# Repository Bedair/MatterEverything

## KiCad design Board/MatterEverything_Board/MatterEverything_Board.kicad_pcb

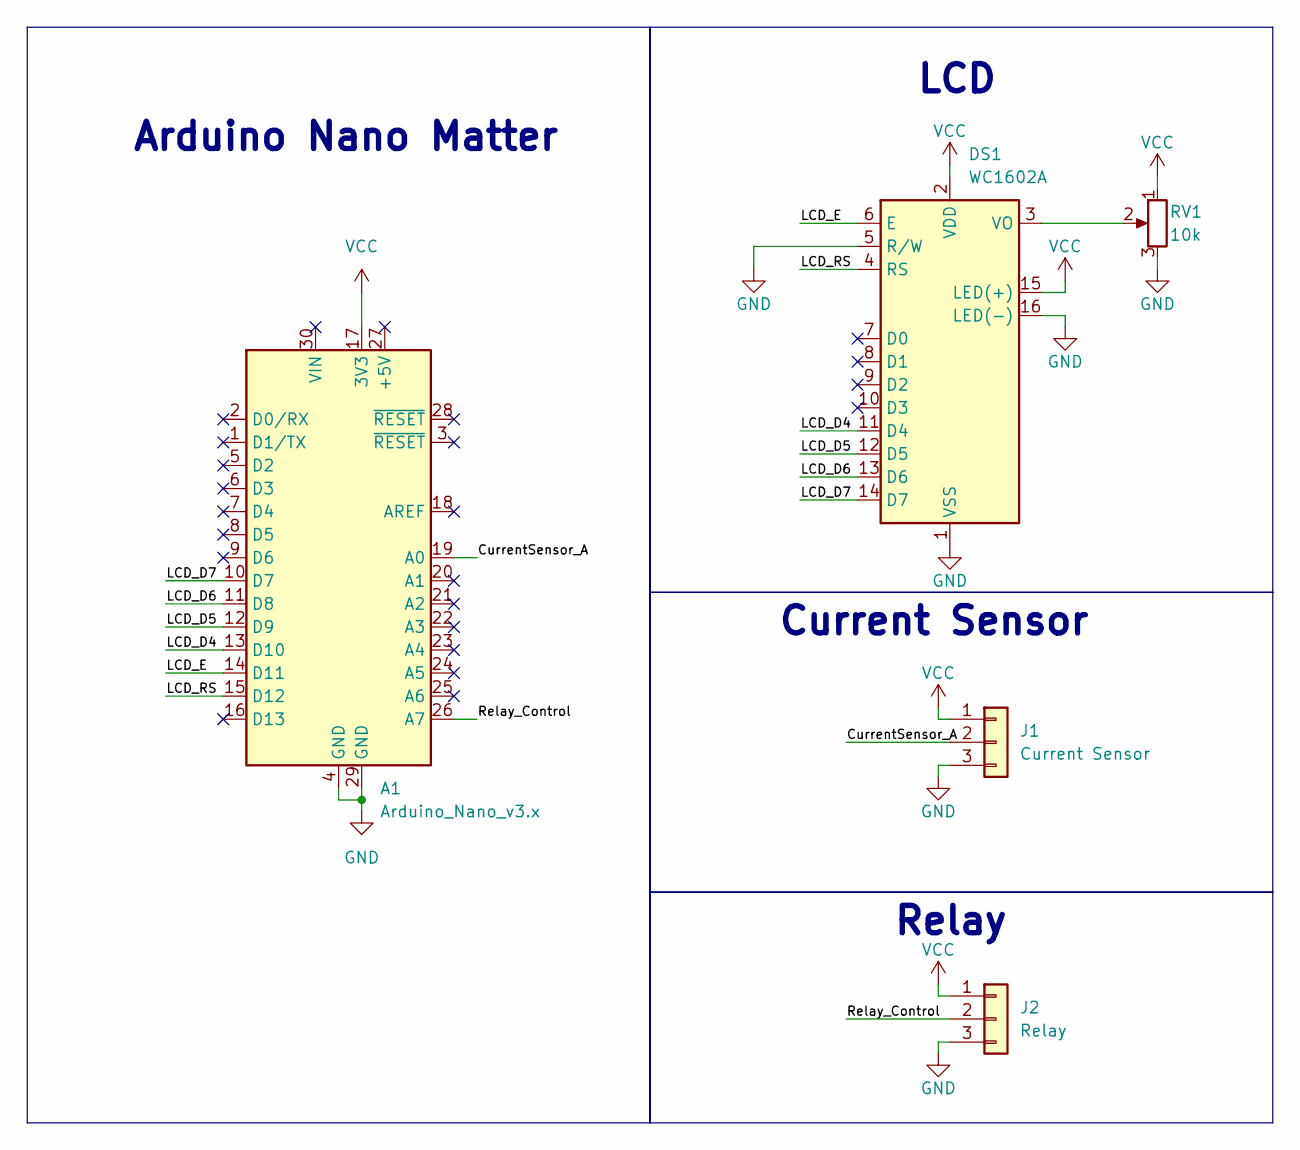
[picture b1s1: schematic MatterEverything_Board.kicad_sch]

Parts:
A1: Arduino_Nano_v3.x; Arduino_Nano
DS1: WC1602A
J1: Current Sensor; PinHeader_1x03_P2.54mm_Vertical
J2: Relay; PinHeader_1x03_P2.54mm_Vertical
RV1: 10k; Potentiometer_Runtron_RM-065_Vertical

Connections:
/CurrentSensor_A: A1.19 (A0), J1.2
/LCD_D4: A1.13 (D10), DS1.11 (D4)
/LCD_D5: A1.12 (D9), DS1.12 (D5)
/LCD_D6: A1.11 (D8), DS1.13 (D6)
/LCD_D7: A1.10 (D7), DS1.14 (D7)
/LCD_E: A1.14 (D11), DS1.6 (E)
/LCD_RS: A1.15 (D12), DS1.4 (RS)
/Relay_Control: A1.26 (A7), J2.2
GND: A1.4 (GND), A1.29 (GND), DS1.1 (VSS), DS1.5 (R/W), DS1.16 (LED(-)), J1.3, J2.3, RV1.3
unnamed: DS1.3 (VO), RV1.2
VCC: A1.17 (3V3), DS1.2 (VDD), DS1.15 (LED(+)), J1.1, J2.1, RV1.1

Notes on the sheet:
Relay
Current Sensor
Arduino Nano Matter
LCD

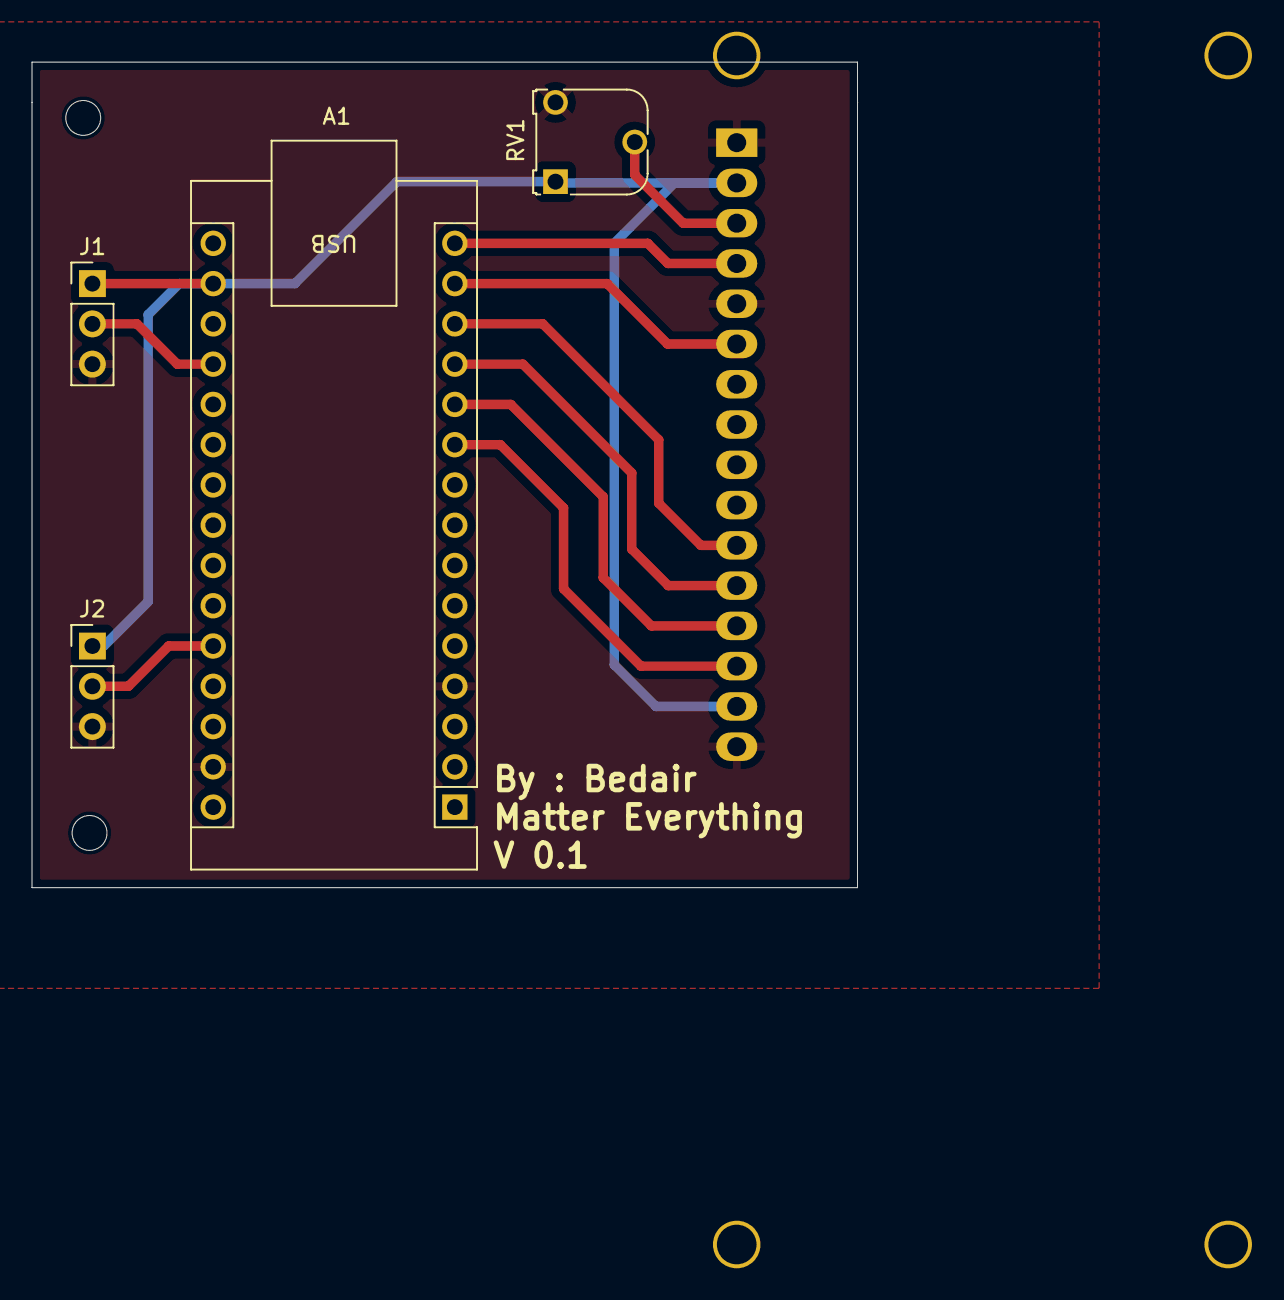
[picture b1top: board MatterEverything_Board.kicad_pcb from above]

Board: 4 copper layers, 52.1 x 52.1 mm, 5 parts (1 on the bottom side), 11 nets.

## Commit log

2024-09-21 Design board file, and generate Gerbers files
2024-09-24 Create the Project Enclosure
2024-10-09 Create initial Arduino script.
2024-10-09 Add implementation for Relay control
2024-10-19 Add Current Measurements functionality
2024-10-19 Update the application based on Matterlightbulb example
2024-10-19 Set the cut low current
2024-10-19 Add images
